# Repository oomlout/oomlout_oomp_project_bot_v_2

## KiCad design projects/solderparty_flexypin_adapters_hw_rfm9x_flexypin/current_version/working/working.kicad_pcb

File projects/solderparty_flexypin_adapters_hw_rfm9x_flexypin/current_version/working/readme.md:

# flexypin_adapters_hw
 
## summary 
* id: solderparty_flexypin_adapters_hw_rfm9x_flexypin
* user: solderparty
* name: flexypin_adapters_hw
* board: rfm9x_flexypin
* repo: https://github.com/solderparty/flexypin_adapters_hw
* src_file_repo_kicad_pcb: RFM9x_flexypin/RFM9x_flexypin.kicad_pcb
* src_file_repo_kicad_pcb_link: https://github.com/solderparty/flexypin_adapters_hw/tree/main/RFM9x_flexypin/RFM9x_flexypin.kicad_pcb
* src_file_repo_kicad_sch: RFM9x_flexypin/RFM9x_flexypin.kicad_sch
* src_file_repo_kicad_sch_link: https://github.com/solderparty/flexypin_adapters_hw/tree/main/RFM9x_flexypin/RFM9x_flexypin.kicad_sch

* src_file_repo_sch: 
* src_file_repo_sch_link: https://github.com/solderparty/flexypin_adapters_hw/tree/main/
* full details link: https://github.com/oomlout/oomlout_oomp_project_bot_v_2/tree/main/projects/solderparty_flexypin_adapters_hw_rfm9x_flexypin/current_version/working  

## schematic  
  
[schematic (pdf)](working_schematic.pdf) 

## pcb  

[board (pdf)](working.pdf)  

## working_bom
| Id | Designator | Footprint | Quantity | Designation | Supplier and ref |  | None | 
| --- | --- | --- | --- | --- | --- | --- | --- | 
| 1 | J8,J3,J7,J5,J4,J6,J2,J9 | FlexyPin_1x02_P2.00mm | 8 | Conn_01x02 |  |  | [''] | 
| 2 | J10,J1 | PinHeader_1x08_P2.54mm_Vertical | 2 | Conn_01x08 |  |  | [''] | 
| 3 | G***,G*** | SolderParty-New-Logo_7.5x6.4mm_SilkScreen | 2 | LOGO |  |  | [''] | 
| 4 | REF** | Fiducial_0.5mm_Mask1.5mm | 1 | Fiducial_0.5mm_Mask1.5mm |  |  | [''] | 

## bom_schematic
| Ref | Qnty | Value | Cmp name | Footprint | Description | Vendor | DNP | 
| --- | --- | --- | --- | --- | --- | --- | --- | 
| J1, J10 | 2 | Conn_01x08 | Conn_01x08 | Connector_PinHeader_2.54mm:PinHeader_1x08_P2.54mm_Vertical | Generic connector, single row, 01x08, script generated (kicad-library-utils/schlib/autogen/connector/) |  |  | 
| J2, J3, J4, J5, J6, J7, J8, J9 | 8 | Conn_01x02 | Conn_01x02 | FlexyPin:FlexyPin_1x02_P2.00mm | Generic connector, single row, 01x02, script generated (kicad-library-utils/schlib/autogen/connector/) |  |  |

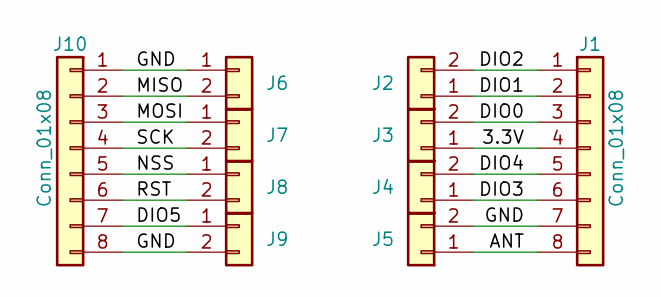
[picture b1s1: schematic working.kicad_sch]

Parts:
J1, J10: Conn_01x08; PinHeader_1x08_P2.54mm_Vertical
J2, J3, J4, J5, J6, J7, J8, J9: Conn_01x02; FlexyPin_1x02_P2.00mm

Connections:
/3.3V: J1.4, J3.1
/ANT: J1.8, J5.1
/DIO0: J1.3, J3.2
/DIO1: J1.2, J2.1
/DIO2: J1.1, J2.2
/DIO3: J1.6, J4.1
/DIO4: J1.5, J4.2
/DIO5: J9.1, J10.7
/GND: J1.7, J5.2, J6.1, J9.2, J10.1, J10.8
/MISO: J6.2, J10.2
/MOSI: J7.1, J10.3
/NSS: J8.1, J10.5
/RST: J8.2, J10.6
/SCK: J7.2, J10.4

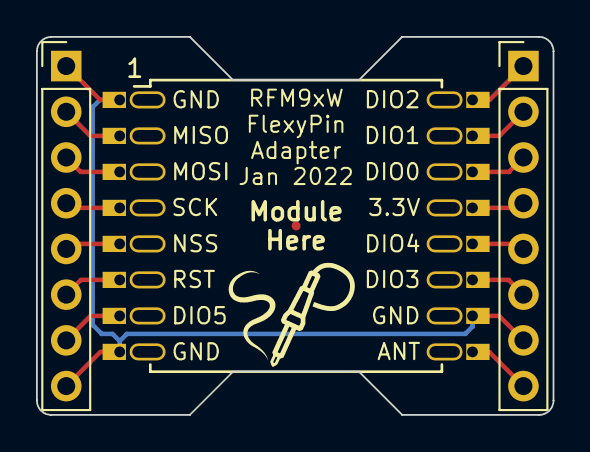
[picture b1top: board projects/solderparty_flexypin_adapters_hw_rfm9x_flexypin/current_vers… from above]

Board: 2 copper layers, 28.7 x 21.0 mm, 10 parts (0 on the bottom side), 14 nets.

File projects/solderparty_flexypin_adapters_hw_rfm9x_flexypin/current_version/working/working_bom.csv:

"Id";"Designator";"Footprint";"Quantity";"Designation";"Supplier and ref";
1;"J8,J3,J7,J5,J4,J6,J2,J9";"FlexyPin_1x02_P2.00mm";8;"Conn_01x02";;;
2;"J10,J1";"PinHeader_1x08_P2.54mm_Vertical";2;"Conn_01x08";;;
3;"G***,G***";"SolderParty-New-Logo_7.5x6.4mm_SilkScreen";2;"LOGO";;;
4;"REF**";"Fiducial_0.5mm_Mask1.5mm";1;"Fiducial_0.5mm_Mask1.5mm";;;

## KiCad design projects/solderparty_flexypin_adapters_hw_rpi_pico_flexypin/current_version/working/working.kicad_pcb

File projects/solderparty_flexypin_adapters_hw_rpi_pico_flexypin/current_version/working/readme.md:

# flexypin_adapters_hw
 
## summary 
* id: solderparty_flexypin_adapters_hw_rpi_pico_flexypin
* user: solderparty
* name: flexypin_adapters_hw
* board: rpi_pico_flexypin
* repo: https://github.com/solderparty/flexypin_adapters_hw
* src_file_repo_kicad_pcb: rpi_pico_flexypin/rpi_pico_flexypin.kicad_pcb
* src_file_repo_kicad_pcb_link: https://github.com/solderparty/flexypin_adapters_hw/tree/main/rpi_pico_flexypin/rpi_pico_flexypin.kicad_pcb
* src_file_repo_kicad_sch: rpi_pico_flexypin/rpi_pico_flexypin.kicad_sch
* src_file_repo_kicad_sch_link: https://github.com/solderparty/flexypin_adapters_hw/tree/main/rpi_pico_flexypin/rpi_pico_flexypin.kicad_sch

* src_file_repo_sch: 
* src_file_repo_sch_link: https://github.com/solderparty/flexypin_adapters_hw/tree/main/
* full details link: https://github.com/oomlout/oomlout_oomp_project_bot_v_2/tree/main/projects/solderparty_flexypin_adapters_hw_rpi_pico_flexypin/current_version/working  

## schematic  
  
[schematic (pdf)](working_schematic.pdf) 

## pcb  

[board (pdf)](working.pdf)  

## working_bom
| Id | Designator | Footprint | Quantity | Designation | Supplier and ref |  | None | 
| --- | --- | --- | --- | --- | --- | --- | --- | 
| 1 | J3,J1 | FlexyPin_1x20_P2.54mm | 2 | Conn_01x20 |  |  | [''] | 
| 2 | U1 | RaspberryPi_Pico | 1 | RaspberryPi_Pico |  |  | [''] | 
| 3 | J2 | FlexyPin_1x03_P2.54mm | 1 | Conn_01x03 |  |  | [''] | 
| 4 | SW1 | SW_PUSH_6mm | 1 | SW_RST |  |  | [''] | 
| 5 | G***,G*** | SolderParty-New-Logo_7.5x6.4mm_SilkScreen | 2 | LOGO |  |  | [''] | 
| 6 | G***,G*** | SolderParty-New-Logo_3x2.5mm_SilkScreen | 2 | LOGO |  |  | [''] | 
| 7 | J4,J5 | PinHeader_1x18_P2.54mm_Vertical | 2 | Conn_01x17 |  |  | [''] | 

## bom_schematic
| Ref | Qnty | Value | Cmp name | Footprint | Description | Vendor | DNP | 
| --- | --- | --- | --- | --- | --- | --- | --- | 
| J1, J3 | 2 | Conn_01x20 | Conn_01x20 | FlexyPin:FlexyPin_1x20_P2.54mm | Generic connector, single row, 01x20, script generated (kicad-library-utils/schlib/autogen/connector/) |  |  | 
| J2 | 1 | Conn_01x03 | Conn_01x03 | FlexyPin:FlexyPin_1x03_P2.54mm | Generic connector, single row, 01x03, script generated (kicad-library-utils/schlib/autogen/connector/) |  |  | 
| J4, J5 | 2 | Conn_01x17 | Conn_01x18 | Connector_PinHeader_2.54mm:PinHeader_1x18_P2.54mm_Vertical | Generic connector, single row, 01x18, script generated (kicad-library-utils/schlib/autogen/connector/) |  |  | 
| SW1 | 1 | SW_RST | SW_SPST | Button_Switch_THT:SW_PUSH_6mm | Single Pole Single Throw (SPST) switch |  |  | 
| U1 | 1 | RaspberryPi_Pico | RaspberryPi_Pico | Module_Extra:RaspberryPi_Pico |  |  |  |

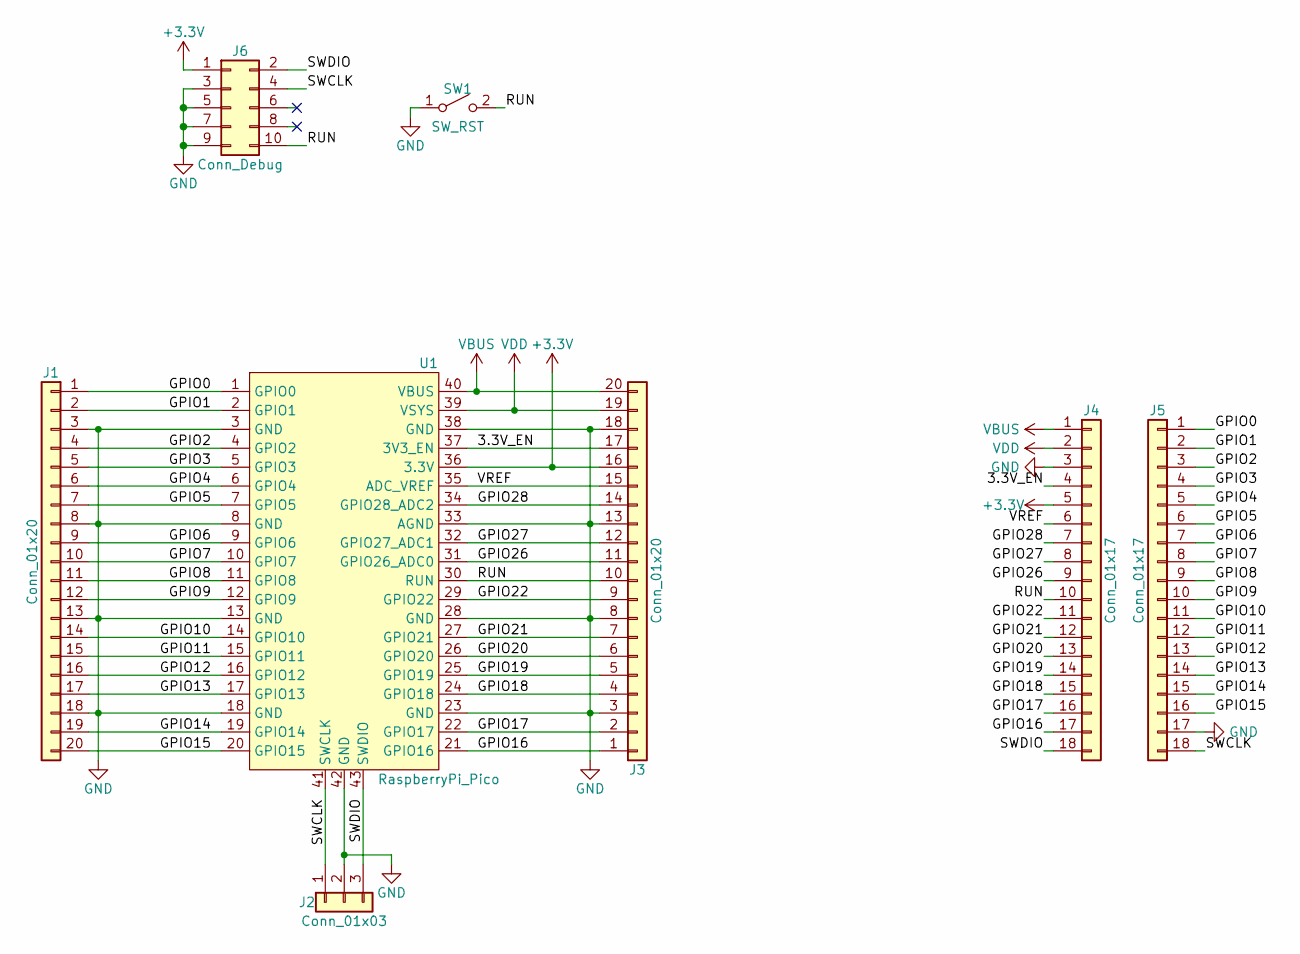
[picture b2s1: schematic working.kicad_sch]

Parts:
J1, J3: Conn_01x20; FlexyPin_1x20_P2.54mm
J2: Conn_01x03; FlexyPin_1x03_P2.54mm
J4, J5: Conn_01x17; PinHeader_1x18_P2.54mm_Vertical
J6: Conn_Debug; PinHeader_2x05_P1.27mm_Vertical_SMD_IDC
SW1: SW_RST; SW_PUSH_6mm
U1: RaspberryPi_Pico

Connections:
+3V3: J3.16, J4.5, J6.1, U1.36 (3.3V)
/3.3V_EN: J3.17, J4.4, U1.37 (3V3_EN)
/GPIO0: J1.1, J5.1, U1.1 (GPIO0)
/GPIO1: J1.2, J5.2, U1.2 (GPIO1)
/GPIO2: J1.4, J5.3, U1.4 (GPIO2)
/GPIO3: J1.5, J5.4, U1.5 (GPIO3)
/GPIO4: J1.6, J5.5, U1.6 (GPIO4)
/GPIO5: J1.7, J5.6, U1.7 (GPIO5)
/GPIO6: J1.9, J5.7, U1.9 (GPIO6)
/GPIO7: J1.10, J5.8, U1.10 (GPIO7)
/GPIO8: J1.11, J5.9, U1.11 (GPIO8)
/GPIO9: J1.12, J5.10, U1.12 (GPIO9)
/GPIO10: J1.14, J5.11, U1.14 (GPIO10)
/GPIO11: J1.15, J5.12, U1.15 (GPIO11)
/GPIO12: J1.16, J5.13, U1.16 (GPIO12)
/GPIO13: J1.17, J5.14, U1.17 (GPIO13)
/GPIO14: J1.19, J5.15, U1.19 (GPIO14)
/GPIO15: J1.20, J5.16, U1.20 (GPIO15)
/GPIO16: J3.1, J4.17, U1.21 (GPIO16)
/GPIO17: J3.2, J4.16, U1.22 (GPIO17)
/GPIO18: J3.4, J4.15, U1.24 (GPIO18)
/GPIO19: J3.5, J4.14, U1.25 (GPIO19)
/GPIO20: J3.6, J4.13, U1.26 (GPIO20)
/GPIO21: J3.7, J4.12, U1.27 (GPIO21)
/GPIO22: J3.9, J4.11, U1.29 (GPIO22)
/GPIO26: J3.11, J4.9, U1.31 (GPIO26_ADC0)
/GPIO27: J3.12, J4.8, U1.32 (GPIO27_ADC1)
/GPIO28: J3.14, J4.7, U1.34 (GPIO28_ADC2)
/RUN: J3.10, J4.10, J6.10, SW1.2 (B), U1.30 (RUN)
/SWCLK: J2.1, J5.18, J6.4, U1.41 (SWCLK)
/SWDIO: J2.3, J4.18, J6.2, U1.43 (SWDIO)
/VREF: J3.15, J4.6, U1.35 (ADC_VREF)
GND: J1.3, J1.8, J1.13, J1.18, J2.2, J3.3, J3.8, J3.13, J3.18, J4.3, J5.17, J6.3, J6.5, J6.7, J6.9, SW1.1 (A), U1.3 (GND), U1.8 (GND), U1.13 (GND), U1.18 (GND), U1.23 (GND), U1.28 (GND), U1.33 (AGND), U1.38 (GND), U1.42 (GND)
VBUS: J3.20, J4.1, U1.40 (VBUS)
VDD: J3.19, J4.2, U1.39 (VSYS)

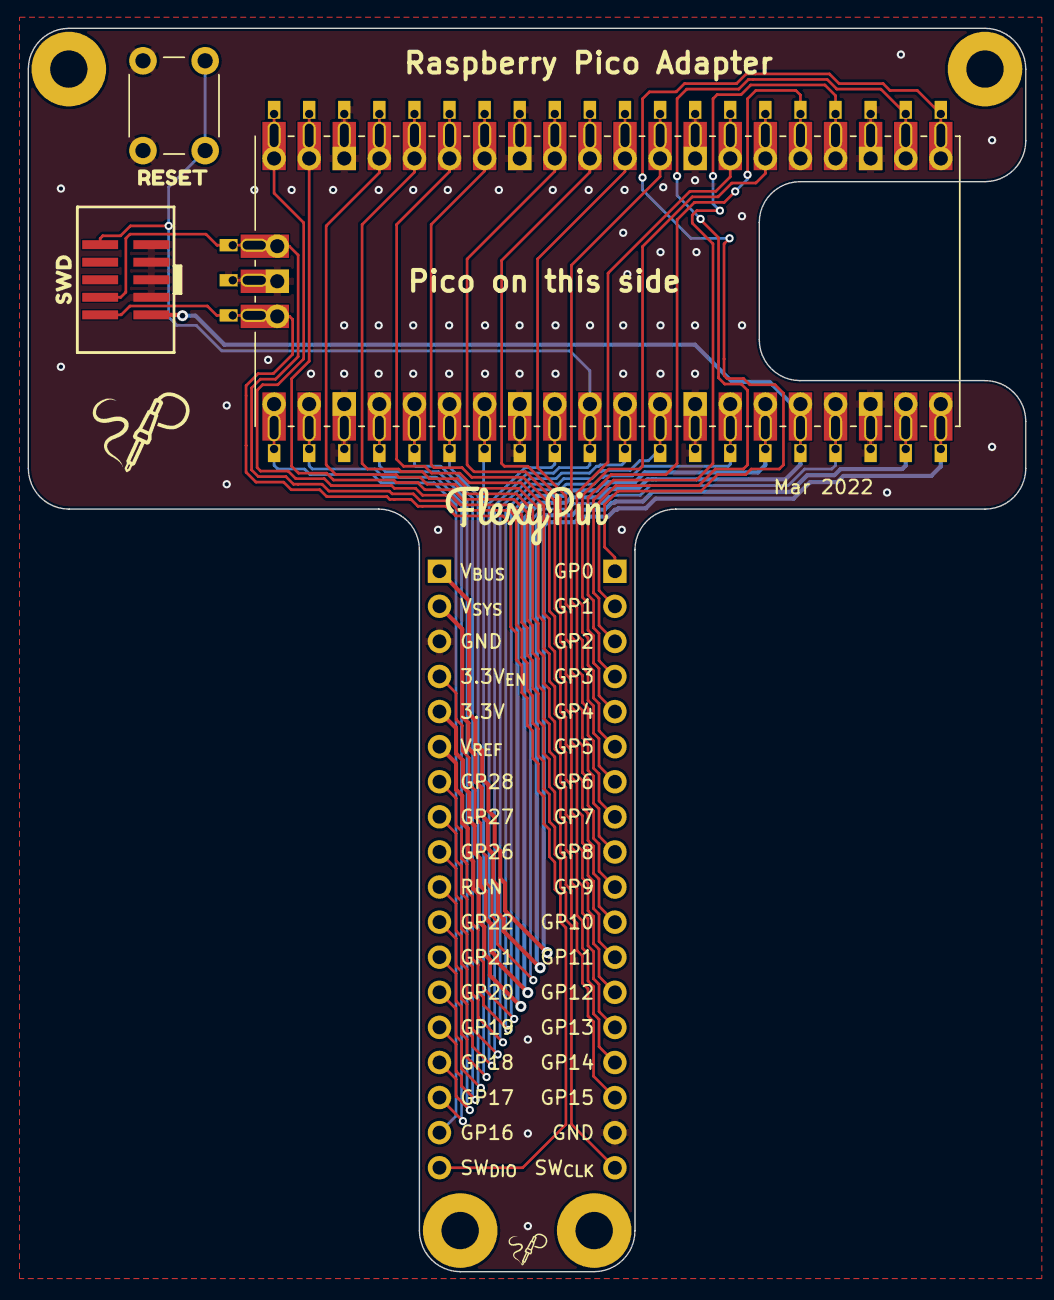
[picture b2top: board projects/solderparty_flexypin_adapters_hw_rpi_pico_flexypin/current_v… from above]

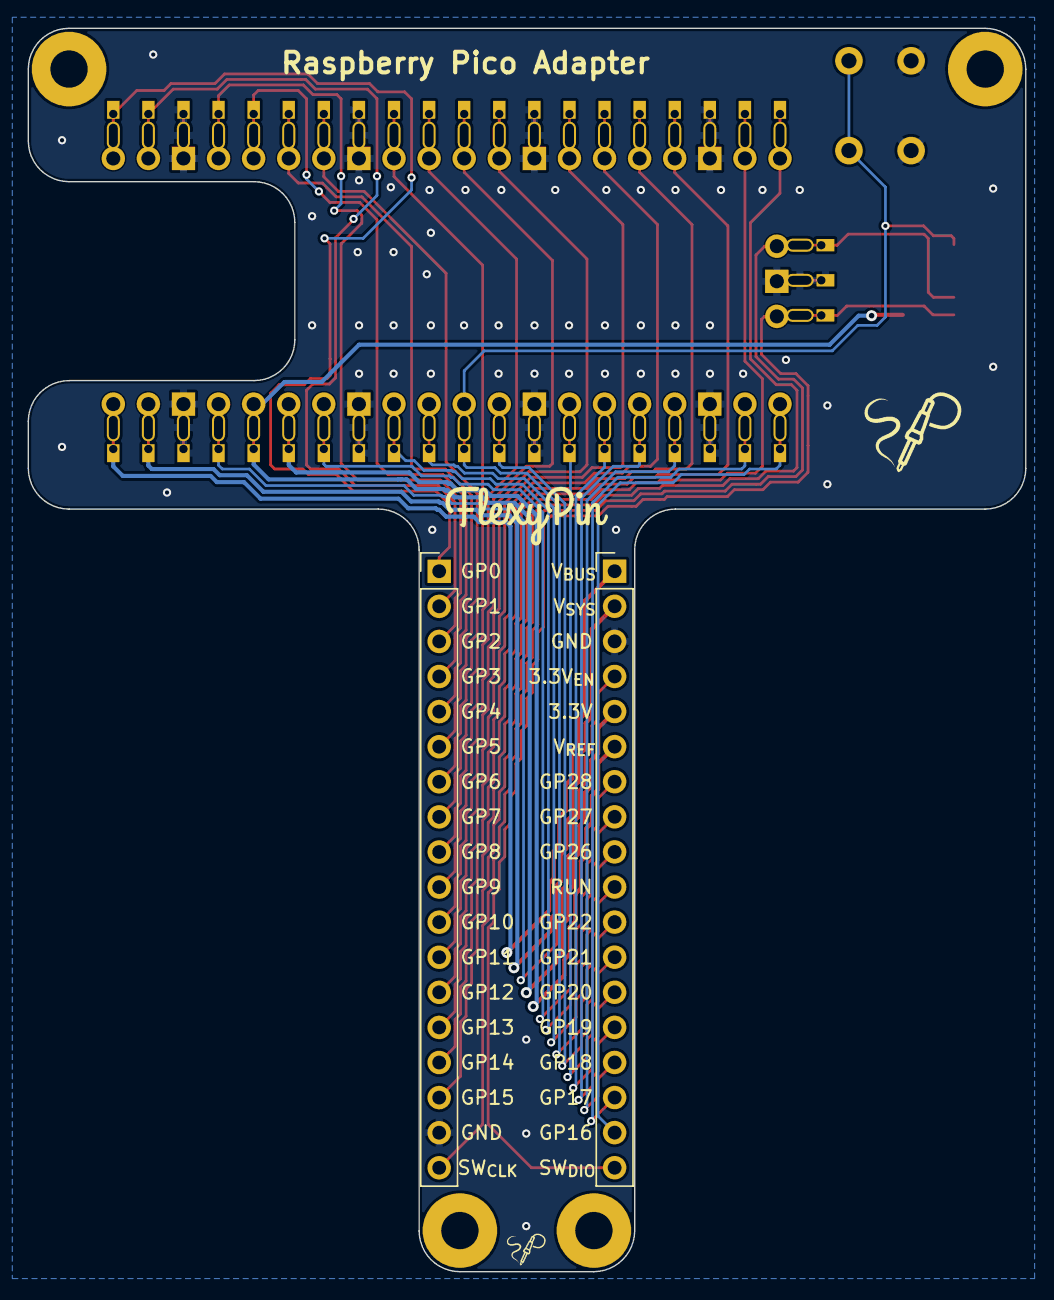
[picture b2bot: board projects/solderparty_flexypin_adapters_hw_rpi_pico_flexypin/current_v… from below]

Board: 2 copper layers, 72.2 x 90.0 mm, 10 parts (2 on the bottom side), 35 nets.

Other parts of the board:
kibuzzard-6227DBEE: G***; kibuzzard-6227DBEE
kibuzzard-6227DBF8: G***; kibuzzard-6227DBF8

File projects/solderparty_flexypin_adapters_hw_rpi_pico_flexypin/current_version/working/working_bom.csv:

"Id";"Designator";"Footprint";"Quantity";"Designation";"Supplier and ref";
1;"J3,J1";"FlexyPin_1x20_P2.54mm";2;"Conn_01x20";;;
2;"U1";"RaspberryPi_Pico";1;"RaspberryPi_Pico";;;
3;"J2";"FlexyPin_1x03_P2.54mm";1;"Conn_01x03";;;
4;"SW1";"SW_PUSH_6mm";1;"SW_RST";;;
5;"G***,G***";"SolderParty-New-Logo_7.5x6.4mm_SilkScreen";2;"LOGO";;;
6;"G***,G***";"SolderParty-New-Logo_3x2.5mm_SilkScreen";2;"LOGO";;;
7;"J4,J5";"PinHeader_1x18_P2.54mm_Vertical";2;"Conn_01x17";;;

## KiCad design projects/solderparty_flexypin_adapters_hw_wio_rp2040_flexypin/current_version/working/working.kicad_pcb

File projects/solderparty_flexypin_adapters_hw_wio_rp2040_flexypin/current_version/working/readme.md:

# flexypin_adapters_hw
 
## summary 
* id: solderparty_flexypin_adapters_hw_wio_rp2040_flexypin
* user: solderparty
* name: flexypin_adapters_hw
* board: wio_rp2040_flexypin
* repo: https://github.com/solderparty/flexypin_adapters_hw
* src_file_repo_kicad_pcb: Wio-RP2040_flexypin/Wio-RP2040_flexypin.kicad_pcb
* src_file_repo_kicad_pcb_link: https://github.com/solderparty/flexypin_adapters_hw/tree/main/Wio-RP2040_flexypin/Wio-RP2040_flexypin.kicad_pcb
* src_file_repo_kicad_sch: Wio-RP2040_flexypin/Wio-RP2040_flexypin.kicad_sch
* src_file_repo_kicad_sch_link: https://github.com/solderparty/flexypin_adapters_hw/tree/main/Wio-RP2040_flexypin/Wio-RP2040_flexypin.kicad_sch

* src_file_repo_sch: 
* src_file_repo_sch_link: https://github.com/solderparty/flexypin_adapters_hw/tree/main/
* full details link: https://github.com/oomlout/oomlout_oomp_project_bot_v_2/tree/main/projects/solderparty_flexypin_adapters_hw_wio_rp2040_flexypin/current_version/working  

## schematic  
  
[schematic (pdf)](working_schematic.pdf) 

## pcb  

[board (pdf)](working.pdf)  

## working_bom
| Id | Designator | Footprint | Quantity | Designation | Supplier and ref |  | None | 
| --- | --- | --- | --- | --- | --- | --- | --- | 
| 1 | J1,J5 | PinHeader_1x15_P2.54mm_Vertical | 2 | Conn_01x15 |  |  | [''] | 
| 2 | G***,G*** | SolderParty-New-Logo_7.5x6.4mm_SilkScreen | 2 | LOGO |  |  | [''] | 
| 3 | J4,J2 | FlexyPin_1x12_P2.00mm | 2 | Conn_01x12 |  |  | [''] | 
| 4 | J3 | FlexyPin_1x08_P2.00mm | 1 | Conn_01x08 |  |  | [''] | 

## bom_schematic
| Ref | Qnty | Value | Cmp name | Footprint | Description | Vendor | DNP | 
| --- | --- | --- | --- | --- | --- | --- | --- | 
| J1, J5 | 2 | Conn_01x15 | Conn_01x15 | Connector_PinHeader_2.54mm:PinHeader_1x15_P2.54mm_Vertical | Generic connector, single row, 01x15, script generated (kicad-library-utils/schlib/autogen/connector/) |  |  | 
| J2, J4 | 2 | Conn_01x12 | Conn_01x12 | FlexyPin:FlexyPin_1x12_P2.00mm | Generic connector, single row, 01x12, script generated (kicad-library-utils/schlib/autogen/connector/) |  |  | 
| J3 | 1 | Conn_01x08 | Conn_01x08 | FlexyPin:FlexyPin_1x08_P2.00mm | Generic connector, single row, 01x08, script generated (kicad-library-utils/schlib/autogen/connector/) |  |  |

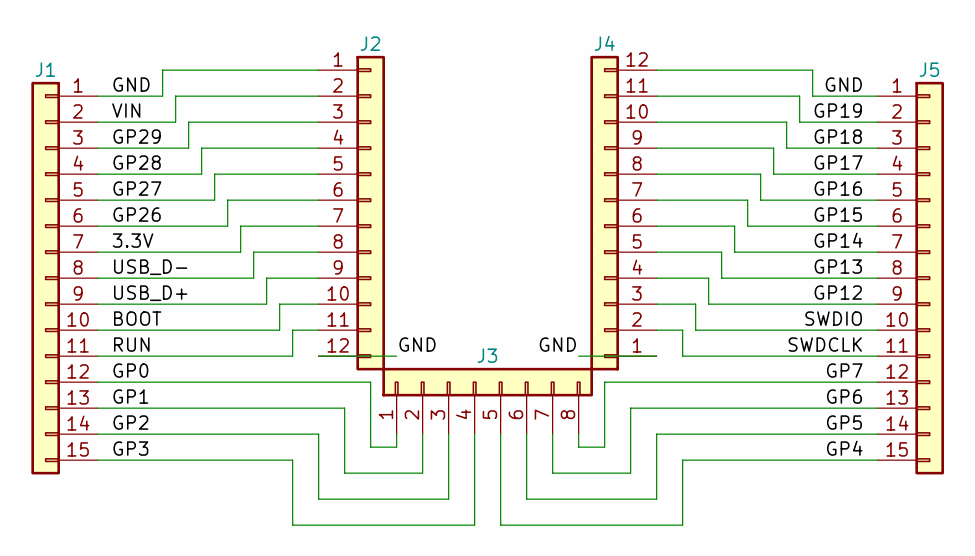
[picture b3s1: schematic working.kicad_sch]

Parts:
J1, J5: Conn_01x15; PinHeader_1x15_P2.54mm_Vertical
J2, J4: Conn_01x12; FlexyPin_1x12_P2.00mm
J3: Conn_01x08; FlexyPin_1x08_P2.00mm

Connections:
/3.3V: J1.7, J2.7
/BOOT: J1.10, J2.10
/GND: J1.1, J2.1, J2.12, J4.1, J4.12, J5.1
/GP0: J1.12, J3.1
/GP1: J1.13, J3.2
/GP2: J1.14, J3.3
/GP3: J1.15, J3.4
/GP4: J3.5, J5.15
/GP5: J3.6, J5.14
/GP6: J3.7, J5.13
/GP7: J3.8, J5.12
/GP12: J4.4, J5.9
/GP13: J4.5, J5.8
/GP14: J4.6, J5.7
/GP15: J4.7, J5.6
/GP16: J4.8, J5.5
/GP17: J4.9, J5.4
/GP18: J4.10, J5.3
/GP19: J4.11, J5.2
/GP26: J1.6, J2.6
/GP27: J1.5, J2.5
/GP28: J1.4, J2.4
/GP29: J1.3, J2.3
/RUN: J1.11, J2.11
/SWDCLK: J4.2, J5.11
/SWDIO: J4.3, J5.10
/USB_D+: J1.9, J2.9
/USB_D-: J1.8, J2.8
/VIN: J1.2, J2.2

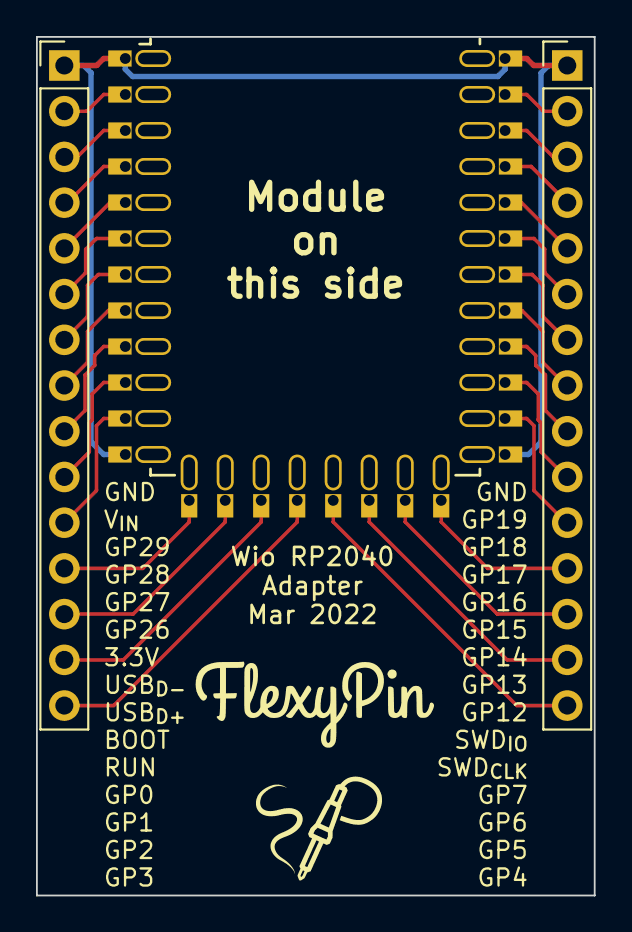
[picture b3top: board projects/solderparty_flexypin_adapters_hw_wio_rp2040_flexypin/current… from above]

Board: 2 copper layers, 31.0 x 47.7 mm, 5 parts (0 on the bottom side), 29 nets.

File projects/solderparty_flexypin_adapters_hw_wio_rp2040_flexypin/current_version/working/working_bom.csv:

"Id";"Designator";"Footprint";"Quantity";"Designation";"Supplier and ref";
1;"J1,J5";"PinHeader_1x15_P2.54mm_Vertical";2;"Conn_01x15";;;
2;"G***,G***";"SolderParty-New-Logo_7.5x6.4mm_SilkScreen";2;"LOGO";;;
3;"J4,J2";"FlexyPin_1x12_P2.00mm";2;"Conn_01x12";;;
4;"J3";"FlexyPin_1x08_P2.00mm";1;"Conn_01x08";;;

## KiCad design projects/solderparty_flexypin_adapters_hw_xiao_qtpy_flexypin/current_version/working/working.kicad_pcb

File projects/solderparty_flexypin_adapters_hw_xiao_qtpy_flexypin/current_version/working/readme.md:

# flexypin_adapters_hw
 
## summary 
* id: solderparty_flexypin_adapters_hw_xiao_qtpy_flexypin
* user: solderparty
* name: flexypin_adapters_hw
* board: xiao_qtpy_flexypin
* repo: https://github.com/solderparty/flexypin_adapters_hw
* src_file_repo_kicad_pcb: xiao_qtpy_flexypin/xiao_qtpy_flexypin.kicad_pcb
* src_file_repo_kicad_pcb_link: https://github.com/solderparty/flexypin_adapters_hw/tree/main/xiao_qtpy_flexypin/xiao_qtpy_flexypin.kicad_pcb
* src_file_repo_kicad_sch: xiao_qtpy_flexypin/xiao_qtpy_flexypin.kicad_sch
* src_file_repo_kicad_sch_link: https://github.com/solderparty/flexypin_adapters_hw/tree/main/xiao_qtpy_flexypin/xiao_qtpy_flexypin.kicad_sch

* src_file_repo_sch: 
* src_file_repo_sch_link: https://github.com/solderparty/flexypin_adapters_hw/tree/main/
* full details link: https://github.com/oomlout/oomlout_oomp_project_bot_v_2/tree/main/projects/solderparty_flexypin_adapters_hw_xiao_qtpy_flexypin/current_version/working  

## schematic  
  
[schematic (pdf)](working_schematic.pdf) 

## pcb  

[board (pdf)](working.pdf)  

## working_bom
| Id | Designator | Footprint | Quantity | Designation | Supplier and ref |  | None | 
| --- | --- | --- | --- | --- | --- | --- | --- | 
| 1 | J4,J8,J7,J2,J3,J6 | FlexyPin_1x02_P2.54mm | 6 | Conn_01x02 |  |  | [''] | 
| 2 | REF** | Fiducial_0.5mm_Mask1.5mm | 1 | Fiducial_0.5mm_Mask1.5mm |  |  | [''] | 
| 3 | J5,J9 | FlexyPin_1x01_P2.54mm | 2 | Conn_01x01 |  |  | [''] | 
| 4 | G***,G*** | SolderParty-New-Logo_7.5x6.4mm_SilkScreen | 2 | LOGO |  |  | [''] | 
| 5 | J10,J1 | PinHeader_1x07_P2.54mm_Vertical | 2 | Conn_01x07 |  |  | [''] | 

## bom_schematic
| Ref | Qnty | Value | Cmp name | Footprint | Description | Vendor | DNP | 
| --- | --- | --- | --- | --- | --- | --- | --- | 
| J1, J10 | 2 | Conn_01x07 | Conn_01x07 | Connector_PinHeader_2.54mm:PinHeader_1x07_P2.54mm_Vertical | Generic connector, single row, 01x07, script generated (kicad-library-utils/schlib/autogen/connector/) |  |  | 
| J2, J3, J4, J6, J7, J8 | 6 | Conn_01x02 | Conn_01x02 | FlexyPin:FlexyPin_1x02_P2.54mm | Generic connector, single row, 01x02, script generated (kicad-library-utils/schlib/autogen/connector/) |  |  | 
| J5, J9 | 2 | Conn_01x01 | Conn_01x01 | FlexyPin:FlexyPin_1x01_P2.54mm | Generic connector, single row, 01x01, script generated (kicad-library-utils/schlib/autogen/connector/) |  |  |

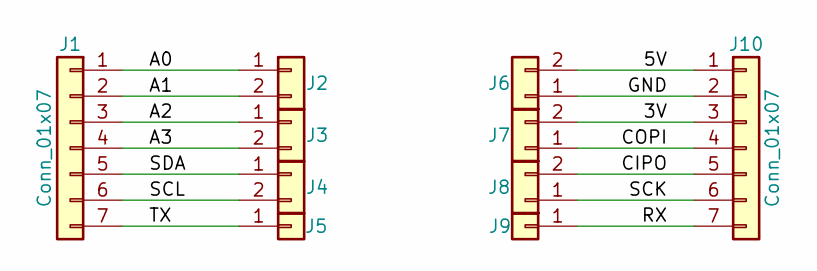
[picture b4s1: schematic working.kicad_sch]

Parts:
J1, J10: Conn_01x07; PinHeader_1x07_P2.54mm_Vertical
J2, J3, J4, J6, J7, J8: Conn_01x02; FlexyPin_1x02_P2.54mm
J5, J9: Conn_01x01; FlexyPin_1x01_P2.54mm

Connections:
/3V: J7.2, J10.3
/5V: J6.2, J10.1
/A0: J1.1, J2.1
/A1: J1.2, J2.2
/A2: J1.3, J3.1
/A3: J1.4, J3.2
/CIPO: J8.2, J10.5
/COPI: J7.1, J10.4
/GND: J6.1, J10.2
/RX: J9.1, J10.7
/SCK: J8.1, J10.6
/SCL: J1.6, J4.2
/SDA: J1.5, J4.1
/TX: J1.7, J5.1

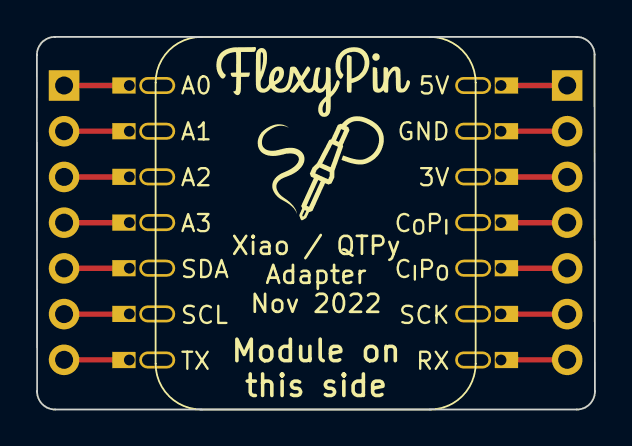
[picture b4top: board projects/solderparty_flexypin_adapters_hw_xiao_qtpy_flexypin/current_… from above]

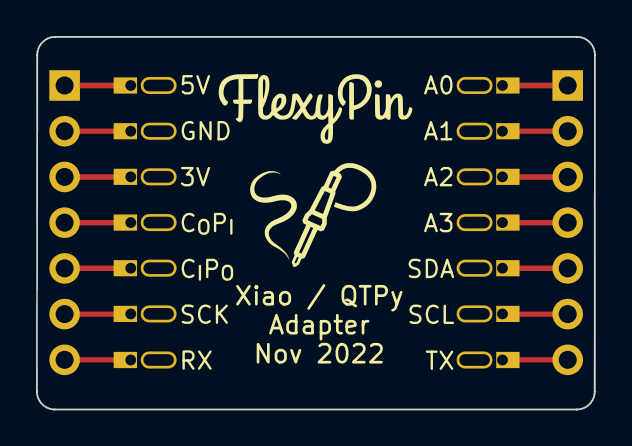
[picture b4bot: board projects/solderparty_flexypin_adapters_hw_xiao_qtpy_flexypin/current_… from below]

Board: 2 copper layers, 31.0 x 20.7 mm, 10 parts (2 on the bottom side), 14 nets.

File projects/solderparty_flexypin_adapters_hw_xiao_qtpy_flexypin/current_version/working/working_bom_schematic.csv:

"Source:","C:\gh\oomlout_oomp_project_bot_v_2\projects\solderparty_flexypin_adapters_hw_xiao_qtpy_flexypin\current_version\working\working.kicad_sch"
"Date:","12/09/2023 07:22:52"
"Tool:","Eeschema 7.0.6"
"Generator:","C:/Program Files/KiCad/7.0/bin/scripting/plugins/bom_csv_grouped_by_value_with_fp.py"
"Component Count:","10"
"Ref","Qnty","Value","Cmp name","Footprint","Description","Vendor","DNP"
"J1, J10","2","Conn_01x07","Conn_01x07","Connector_PinHeader_2.54mm:PinHeader_1x07_P2.54mm_Vertical","Generic connector, single row, 01x07, script generated (kicad-library-utils/schlib/autogen/connector/)","",""
"J2, J3, J4, J6, J7, J8","6","Conn_01x02","Conn_01x02","FlexyPin:FlexyPin_1x02_P2.54mm","Generic connector, single row, 01x02, script generated (kicad-library-utils/schlib/autogen/connector/)","",""
"J5, J9","2","Conn_01x01","Conn_01x01","FlexyPin:FlexyPin_1x01_P2.54mm","Generic connector, single row, 01x01, script generated (kicad-library-utils/schlib/autogen/connector/)","",""

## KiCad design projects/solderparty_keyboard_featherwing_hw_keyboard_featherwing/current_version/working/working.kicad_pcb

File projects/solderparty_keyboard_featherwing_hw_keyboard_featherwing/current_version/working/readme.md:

# keyboard_featherwing_hw
 
## summary 
* id: solderparty_keyboard_featherwing_hw_keyboard_featherwing
* user: solderparty
* name: keyboard_featherwing_hw
* board: keyboard_featherwing
* repo: https://github.com/solderparty/keyboard_featherwing_hw
* src_file_repo_kicad_pcb: keyboard_featherwing.kicad_pcb
* src_file_repo_kicad_pcb_link: https://github.com/solderparty/keyboard_featherwing_hw/tree/master/keyboard_featherwing.kicad_pcb
* src_file_repo_kicad_sch: keyboard.kicad_sch
* src_file_repo_kicad_sch_link: https://github.com/solderparty/keyboard_featherwing_hw/tree/master/keyboard.kicad_sch

* src_file_repo_sch: 
* src_file_repo_sch_link: https://github.com/solderparty/keyboard_featherwing_hw/tree/master/
* full details link: https://github.com/oomlout/oomlout_oomp_project_bot_v_2/tree/main/projects/solderparty_keyboard_featherwing_hw_keyboard_featherwing/current_version/working  

## schematic  
  
[schematic (pdf)](working_schematic.pdf) 

## pcb  

[board (pdf)](working.pdf)  

## working_bom
| Id | Designator | Footprint | Quantity | Designation | Supplier and ref |  | None | 
| --- | --- | --- | --- | --- | --- | --- | --- | 
| 1 | J7 | JST_SH_SM04B-SRSS-TB_1x04-1MP_P1.00mm_Horizontal | 1 | Conn_Stemma_QT |  |  | [''] | 
| 2 | R10,R8,R6,R4,R3,R9 | R_0603_1608Metric | 6 | 10K |  |  | [''] | 
| 3 | SW1 | K3-x245S | 1 | SK-3245S-Lx-B |  |  | [''] | 
| 4 | C6,C11,C12,C1,C4 | C_0603_1608Metric | 5 | 0.1uF |  |  | [''] | 
| 5 | R2,R1 | R_0603_1608Metric | 2 | 4.7K |  |  | [''] | 
| 6 | U4 | ER-CON50HT-1 | 1 | ER-TFT02X |  |  | [''] | 
| 7 | U3 | QFN-20-1EP_4x4mm_P0.5mm_EP2.7x2.7mm | 1 | TSC2004IR |  |  | [''] | 
| 8 | C3 | C_0603_1608Metric | 1 | 1uF |  |  | [''] | 
| 9 | R5 | R_0603_1608Metric | 1 | 1K |  |  | [''] | 
| 10 | U2 | BM14B(0.8)-24DS-0.4V(53) | 1 | BBQ10KBD |  |  | [''] | 
| 11 | C5,C2 | C_0603_1608Metric | 2 | 10uF |  |  | [''] | 
| 12 | Q1,Q2 | SOT-23 | 2 | BSS138 |  |  | [''] | 
| 13 | D3,D2 | D_SOD-323_HandSoldering | 2 | S1JHE |  |  | [''] | 
| 14 | U8 | SOT-353_SC-70-5 | 1 | 74AHCT1G125 |  |  | [''] | 
| 15 | U6 | FeatherWing | 1 | Adafruit_Feather_2X |  |  | [''] | 
| 16 | R7 | R_0603_1608Metric | 1 | 10R |  |  | [''] | 
| 17 | U7 | QFN-48-1EP_7x7mm_P0.5mm_EP5.15x5.15mm | 1 | ATSAMD20G16A |  |  | [''] | 
| 18 | J3 | microSD_HC_Molex_104031-0811 | 1 | Micro_SD_Card_Det |  |  | [''] | 
| 19 | Q3 | Everlight_PT26-21C | 1 | PT26-21C |  |  | [''] | 
| 20 | JP4 | SolderJumper-2_P1.3mm_Open_RoundedPad1.0x1.5mm | 1 | SB_MIC_VDD |  |  | [''] | 
| 21 | SW2 | RMT-CZ66 | 1 | SW_RIGHT1 |  |  | [''] | 
| 22 | SW4 | RMT-CZ66 | 1 | SW_RIGHT2 |  |  | [''] | 
| 23 | SW5 | RMT-CZ66 | 1 | SW_LEFT2 |  |  | [''] | 
| 24 | U1 | SF303GJ26 | 1 | 5-Way_Switch |  |  | [''] | 
| 25 | REF** | Fiducial_0.5mm_Dia_1mm_Outer | 1 | Fiducial_0.5mm_Dia_1mm_Outer |  |  | [''] | 
| 26 | SW3 | RMT-CZ66 | 1 | SW_LEFT1 |  |  | [''] | 
| 27 | D1 | LED_WS2812B_PLCC4_5.0x5.0mm_P3.2mm | 1 | WS2812B |  |  | [''] | 

## bom_schematic
| Ref | Qnty | Value | Cmp name | Footprint | Description | Vendor | DNP | 
| --- | --- | --- | --- | --- | --- | --- | --- | 
| C1, C11, C12 | 3 | 0.1uF | C_Small | Capacitor_SMD:C_0603_1608Metric | Unpolarized capacitor, small symbol |  |  | 
| C2 | 1 | 10uF | C_Small | Capacitor_SMD:C_0603_1608Metric | Unpolarized capacitor, small symbol |  |  | 
| C3 | 1 | 1uF | C_Small | Capacitor_SMD:C_0603_1608Metric | Unpolarized capacitor, small symbol |  |  | 
| JP4 | 1 | SB_MIC_VDD | SolderJumper_2_Open | Jumper:SolderJumper-2_P1.3mm_Open_RoundedPad1.0x1.5mm | Solder Jumper, 2-pole, open |  |  | 
| Q1 | 1 | BSS138 | BSS138 | Package_TO_SOT_SMD:SOT-23 | 50V Vds, 0.22A Id, N-Channel MOSFET, SOT-23 |  |  | 
| R4 | 1 | 10K | R_Small | Resistor_SMD:R_0603_1608Metric | Resistor, small symbol |  |  | 
| R5 | 1 | 1K | R_Small | Resistor_SMD:R_0603_1608Metric | Resistor, small symbol |  |  | 
| SW2 | 1 | SW_RIGHT1 | SW_SPST | Button_Switch_SMD_Extra:RMT-CZ66 | Single Pole Single Throw (SPST) switch |  |  | 
| SW3 | 1 | SW_LEFT1 | SW_SPST | Button_Switch_SMD_Extra:RMT-CZ66 | Single Pole Single Throw (SPST) switch |  |  | 
| SW4 | 1 | SW_RIGHT2 | SW_SPST | Button_Switch_SMD_Extra:RMT-CZ66 | Single Pole Single Throw (SPST) switch |  |  | 
| SW5 | 1 | SW_LEFT2 | SW_SPST | Button_Switch_SMD_Extra:RMT-CZ66 | Single Pole Single Throw (SPST) switch |  |  | 
| U1 | 1 | 5-Way_Switch | 5-Way_Switch | Button_Switch_SMD_Extra:SF303GJ26 |  |  |  | 
| U2 | 1 | BBQ10KBD | BBQ10KBD | Connector_Hirose_Extra:BM14B(0.8)-24DS-0.4V(53) |  |  |  | 
| U7 | 1 | ATSAMD20G16A | ATSAMD20G16A | Package_DFN_QFN:QFN-48-1EP_7x7mm_P0.5mm_EP5.15x5.15mm |  |  |  |

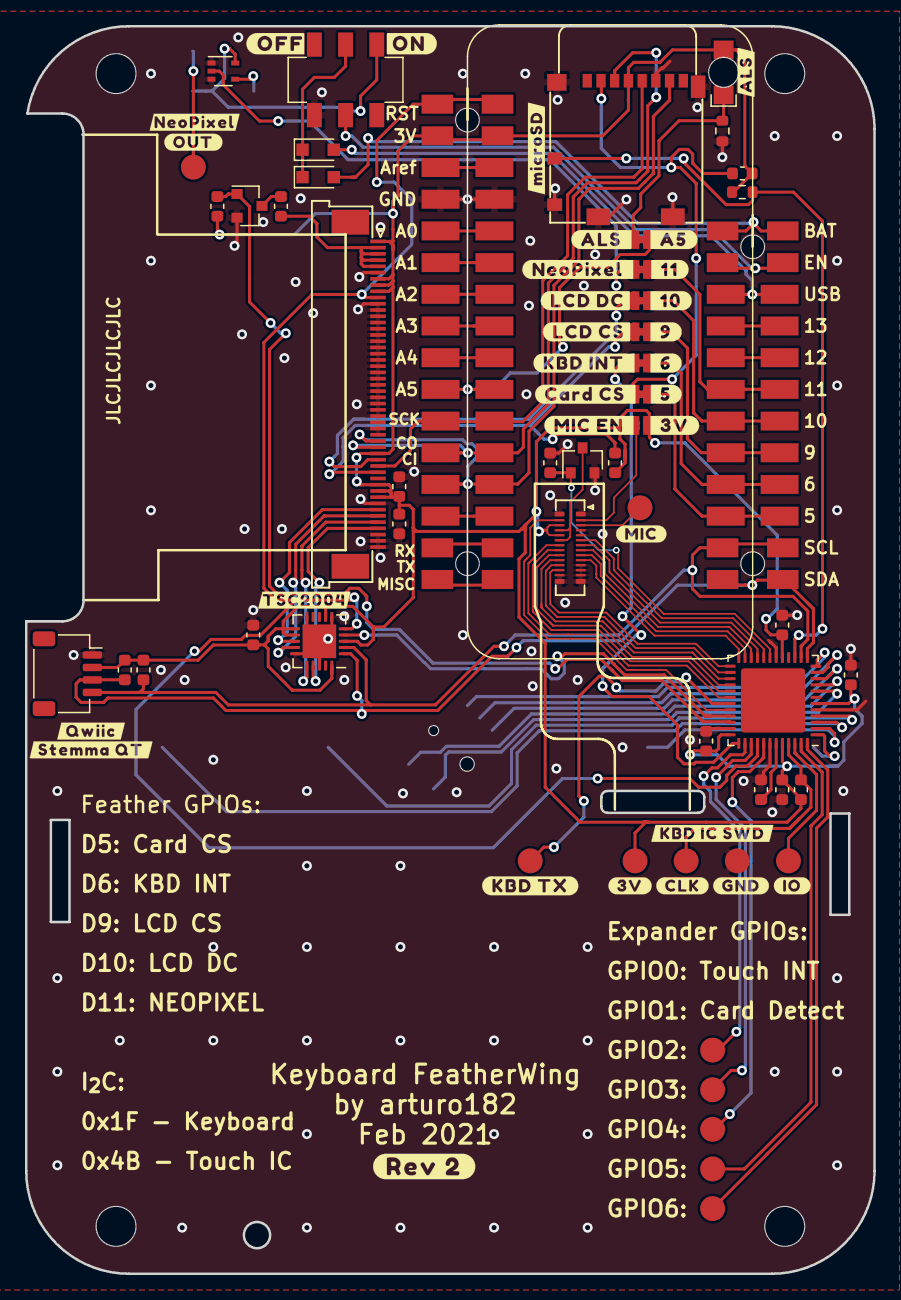
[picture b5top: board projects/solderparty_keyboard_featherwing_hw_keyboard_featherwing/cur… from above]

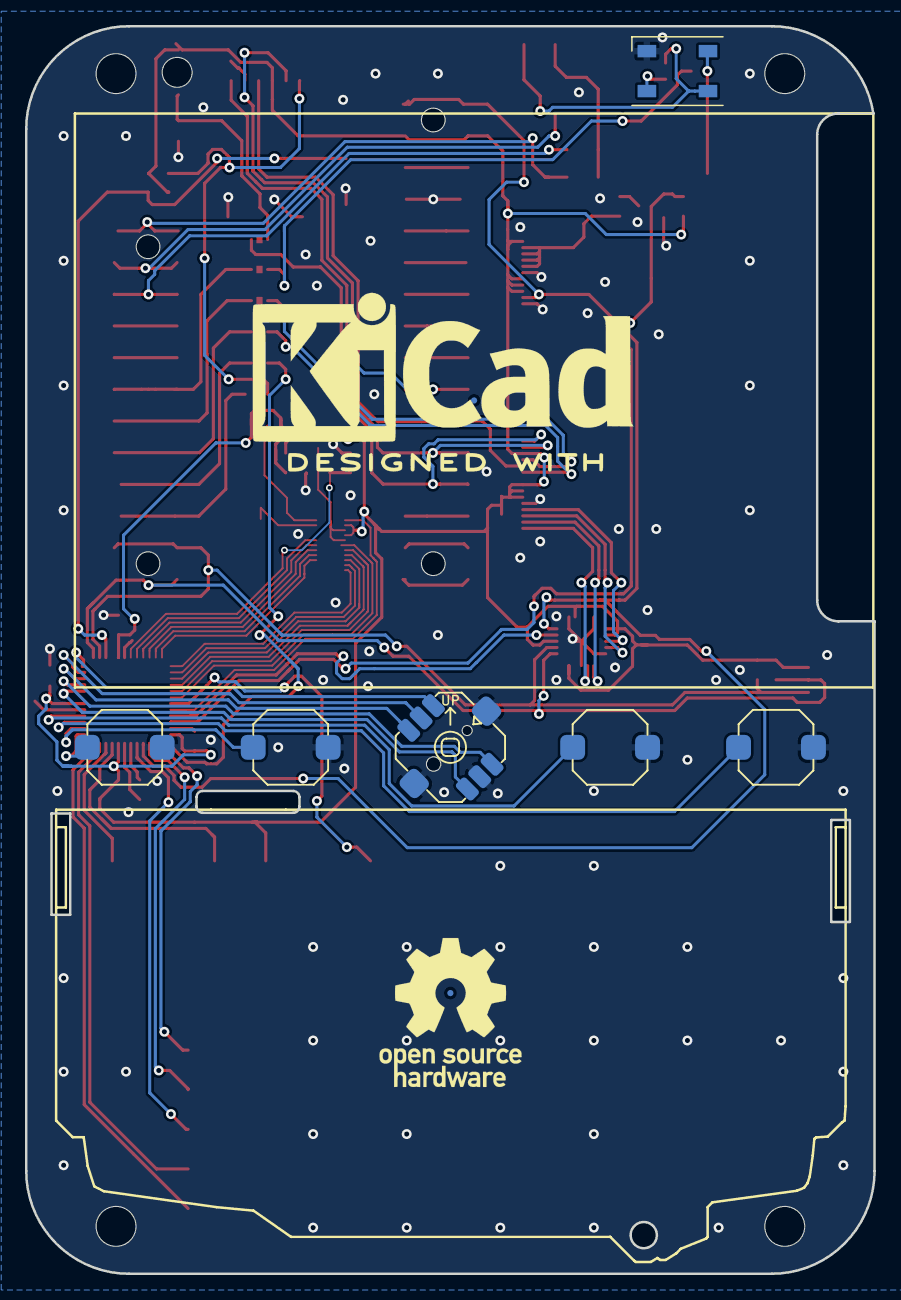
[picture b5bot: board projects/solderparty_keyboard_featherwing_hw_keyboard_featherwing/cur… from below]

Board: 2 copper layers, 68.0 x 100.0 mm, 57 parts (6 on the bottom side), 70 nets.

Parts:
C1, C4, C6, C11, C12: 0.1uF; C_0603_1608Metric
C2, C5: 10uF; C_0603_1608Metric
C3: 1uF; C_0603_1608Metric
D1: WS2812B; LED_WS2812B_PLCC4_5.0x5.0mm_P3.2mm
D2, D3: S1JHE; D_SOD-323_HandSoldering
J3: Micro_SD_Card_Det; microSD_HC_Molex_104031-0811
J7: Conn_Stemma_QT; JST_SH_SM04B-SRSS-TB_1x04-1MP_P1.00mm_Horizontal
JP1: SB_CARD_CS; SolderJumper-2_P1.3mm_Bridged_RoundedPad1.0x1.5mm
JP2: SB_LCD_CS; SolderJumper-2_P1.3mm_Bridged_RoundedPad1.0x1.5mm
JP3: SB_LCD_DC; SolderJumper-2_P1.3mm_Bridged_RoundedPad1.0x1.5mm
JP4: SB_MIC_VDD; SolderJumper-2_P1.3mm_Open_RoundedPad1.0x1.5mm
JP5: SB_KBD_INT; SolderJumper-2_P1.3mm_Bridged_RoundedPad1.0x1.5mm
JP6: SB_NEOPIXEL; SolderJumper-2_P1.3mm_Bridged_RoundedPad1.0x1.5mm
JP7: SB_ALS; SolderJumper-2_P1.3mm_Bridged_RoundedPad1.0x1.5mm
Q1, Q2: BSS138; SOT-23
Q3: PT26-21C; Everlight_PT26-21C
R1, R2: 4.7K; R_0603_1608Metric
R3, R4, R6, R8, R9, R10: 10K; R_0603_1608Metric
R5: 1K; R_0603_1608Metric
R7: 10R; R_0603_1608Metric
SW1: SK-3245S-Lx-B; K3-x245S
SW2: SW_RIGHT1; RMT-CZ66
SW3: SW_LEFT1; RMT-CZ66
SW4: SW_RIGHT2; RMT-CZ66
SW5: SW_LEFT2; RMT-CZ66
TP1: TP_MIC; TestPoint_Pad_D2.0mm
TP2: TP_KBD_SWCLK; TestPoint_Pad_D2.0mm
TP3: TP_KBD_SWDIO; TestPoint_Pad_D2.0mm
TP4: TP_KBD_TX; TestPoint_Pad_D2.0mm
TP5: TP_NEOPIXEL_OUT; TestPoint_Pad_D2.0mm
TP8: TP_GPIO2; TestPoint_Pad_D2.0mm
TP9: TP_KBD_3V; TestPoint_Pad_D2.0mm
TP10: TP_KBD_GND; TestPoint_Pad_D2.0mm
TP11: TP_GPIO3; TestPoint_Pad_D2.0mm
TP12: TP_GPIO4; TestPoint_Pad_D2.0mm
TP13: TP_GPIO5; TestPoint_Pad_D2.0mm
TP14: TP_GPIO6; TestPoint_Pad_D2.0mm
U1: 5-Way_Switch; SF303GJ26
U2: BBQ10KBD; BM14B(0.8)-24DS-0.4V(53)
U3: TSC2004IR; QFN-20-1EP_4x4mm_P0.5mm_EP2.7x2.7mm
U4: ER-TFT02X; ER-CON50HT-1
U6: Adafruit_Feather_2X; FeatherWing
U7: ATSAMD20G16A; QFN-48-1EP_7x7mm_P0.5mm_EP5.15x5.15mm
U8: 74AHCT1G125; SOT-353_SC-70-5

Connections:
+3V3: C1.1, C2.1, C4.1, C5.1, C6.1, C11.1, C12.1, J3.4 (VDD), J7.2, JP4.1 (A), Q3.1, R1.1, R2.1, R3.2, R5.1, R6.2, R8.2, R9.2, TP9.1, U2.24 (LEDA_3_4), U2.26 (LEDA_1_2), U3.3 (AD1), U3.7 (VDD), U3.11 (VREF), U3.12 (VDD), U3.20 (AD0), U4.1 (LEDK/A), U4.7 (IM1), U4.8 (IM2), U4.9 (IM3), U4.35 (RD), U4.40 (VDDI), U4.41 (VDDI), U4.42 (VCI), U6.2 (3V), U7.6 (VDD), U7.17 (VDDIO), U7.36 (VDDIO), U7.44 (VDDIN)
+5V: D1.1 (VDD), SW1.6 (C), U8.5 (VCC)
+BATT: D3.2 (A), U6.28 (VBAT)
/A5: JP7.1 (A), U6.10 (A5)
/ALS: JP7.2 (B), Q3.2, R10.1
/CARD_CIPO: J3.7 (DAT0), U4.33 (SDO), U6.13 (MISO)
/CARD_CLK: J3.5 (CLK), U4.37 (SCL), U6.11 (SCK)
/CARD_COPI: J3.3 (CMD), U4.34 (SDI/SDA), U6.12 (MOSI)
/CARD_CS: J3.2 (DAT3/CD), JP1.2 (B), R3.1
/CARD_DET: J3.10 (DET_A), R9.1, U7.15 (PA10)
/EN: SW1.2 (B), U6.27 (EN)
/GPIO5: JP1.1 (A), U6.19 (GPIO5)
/GPIO6: JP5.1 (A), U6.20 (GPIO6)
/GPIO9: JP2.1 (A), U6.21 (GPIO9)
/GPIO10: JP3.1 (A), U6.22 (GPIO10)
/GPIO11: JP6.1 (A), U6.23 (GPIO11)
/KBD_INT: JP5.2 (B), U7.37 (PB22)
/KBD_RESET: U3.5 (~RESET~), U4.10 (RESET), U6.1 (~RESET~), U7.40 (~RESET~)
/KBD_SCL: J7.4, R2.2, U3.2 (SCL), U6.18 (SCL), U7.14 (PA09)
/KBD_SDA: J7.3, R1.2, U3.1 (SDA), U6.17 (SDA), U7.13 (PA08)
/Keyboard/BL_CTRL: Q1.1 (G), R4.2, U7.19 (PB10)
/Keyboard/BTN_LEFT1: SW3.2 (B), U7.1 (PA00)
/Keyboard/BTN_LEFT2: SW5.2 (B), U7.2 (PA01)
/Keyboard/BTN_RIGHT1: SW2.2 (B), U7.3 (PA02)
/Keyboard/BTN_RIGHT2: SW4.2 (B), U7.4 (PA03)
/Keyboard/JOY_CENTER: U1.2 (Center), U7.11 (PA06)
/Keyboard/JOY_DOWN: U1.6 (Down), U7.8 (PB09)
/Keyboard/JOY_LEFT: U1.3 (Left), U7.10 (PA05)
/Keyboard/JOY_RIGHT: U1.4 (Right), U7.9 (PA04)
/Keyboard/JOY_UP: U1.1 (Up), U7.12 (PA07)
/Keyboard/KBD_COL1: U2.7 (COL1), U7.21 (PA12)
/Keyboard/KBD_COL2: U2.9 (COL2), U7.23 (PA14)
/Keyboard/KBD_COL3: U2.10 (COL3), U7.24 (PA15)
/Keyboard/KBD_COL4: U2.17 (COL4), U7.25 (PA16)
/Keyboard/KBD_COL5: U2.19 (COL5), U7.27 (PA18)
/Keyboard/KBD_ROW1: U2.6 (ROW1), U7.20 (PB11)
/Keyboard/KBD_ROW2: U2.8 (ROW2), U7.22 (PA13)
/Keyboard/KBD_ROW3: U2.18 (ROW3), U7.26 (PA17)
/Keyboard/KBD_ROW4: U2.20 (ROW4), U7.28 (PA19)
/Keyboard/KBD_ROW5: U2.21 (ROW5), U7.29 (PA20)
/Keyboard/KBD_ROW6: U2.22 (ROW6), U7.30 (PA21)
/Keyboard/KBD_ROW7: U2.27 (ROW7), U7.32 (PA23)
/LCD_BL_CTRL: Q2.1 (G), R6.1, U7.34 (PA25)
/LCD_CS: JP2.2 (B), R8.1, U4.38 (CS)
/LCD_DC: JP3.2 (B), U4.36 (DC)
/NEOPIXEL: JP6.2 (B), U8.2
/TP_INT: U3.4 (~PINTDAV~), U7.33 (PA24)
/TP_XM: U3.16 (X-), U4.46 (X-)
/TP_XP: U3.13 (X+), U4.44 (X+)
/TP_YM: U3.17 (Y-), U4.47 (Y-)
/TP_YP: U3.14 (Y+), U4.45 (Y+)
GND: C1.2, C2.2, C3.2, C4.2, C5.2, C6.2, C11.2, C12.2, D1.3 (VSS), J3.6 (VSS), J3.9 (DET_B), J3.11 (SHIELD), J7.1, Q1.2 (S), Q2.2 (S), R4.1, R10.2, SW1.1 (A), SW2.1 (A), SW3.1 (A), SW4.1 (A), SW5.1 (A), TP10.1, U1.5 (Common), U1.SHIELD, U2.1 (GND), U2.4 (AGND), U2.5 (GND), U2.11 (GND), U2.12 (GND), U2.13 (GND), U2.14 (GND), U2.15 (GND), U2.16 (GND), U2.28 (GND), U3.6 (GND), U3.10 (GND), U3.15 (GND), U3.18 (GND), U3.21 (GND), U4.6 (IM0), U4.11 (VSYNC), U4.12 (HSYNC), U4.13 (DOTCLK), U4.14 (DE), U4.15 (DB17), U4.16 (DB16), U4.17 (DB15), U4.18 (DB14), U4.19 (DB13), U4.20 (DB12), U4.21 (DB11), U4.22 (DB10), U4.23 (DB9), U4.24 (DB8), U4.25 (DB7), U4.26 (DB6), U4.27 (DB5), U4.28 (DB4), U4.29 (DB3), U4.30 (DB2), U4.31 (DB1), U4.32 (DB0), U4.43 (GND), U4.48 (GND), U4.49 (GND), U4.50 (GND), U6.4 (GND), U7.5 (GND), U7.18 (GND), U7.35 (GND), U7.42 (GND), U8.1, U8.3 (GND)
unnamed: C3.1, U7.43 (VDDCORE)
unnamed: D1.2 (DOUT), TP5.1
unnamed: D1.4 (DIN), U8.4
unnamed: D2.1 (K), D3.1 (K), SW1.5 (B)
unnamed: JP4.2 (B), U2.2 (MIC_VDD)
unnamed: Q1.3 (D), U2.23 (LEDK_2_3), U2.25 (LEDK_1_4)
unnamed: Q2.3 (D), R7.2
unnamed: R5.2, TP2.1, U7.45 (SWCLK)
unnamed: R7.1, U4.2 (LEDA/K), U4.3 (LEDA/K), U4.4 (LEDA/K), U4.5 (LEDA/K)
unnamed: TP1.1, U2.3 (MIC)
unnamed: TP3.1, U7.46 (SWDIO)
unnamed: TP4.1, U7.31 (PA22)
unnamed: TP8.1, U7.38 (PB23)
unnamed: TP11.1, U7.39 (PA27)
unnamed: TP12.1, U7.41 (PA28)
unnamed: TP13.1, U7.47 (PB02)
unnamed: TP14.1, U7.48 (PB03)
VBUS: D2.2 (A), U6.26 (VUSB)
